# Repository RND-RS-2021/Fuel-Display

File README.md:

# Fuel-Display
Fuel Display using OLED 128x64 
# Research and Development PT. Radiator Springs Indonesia

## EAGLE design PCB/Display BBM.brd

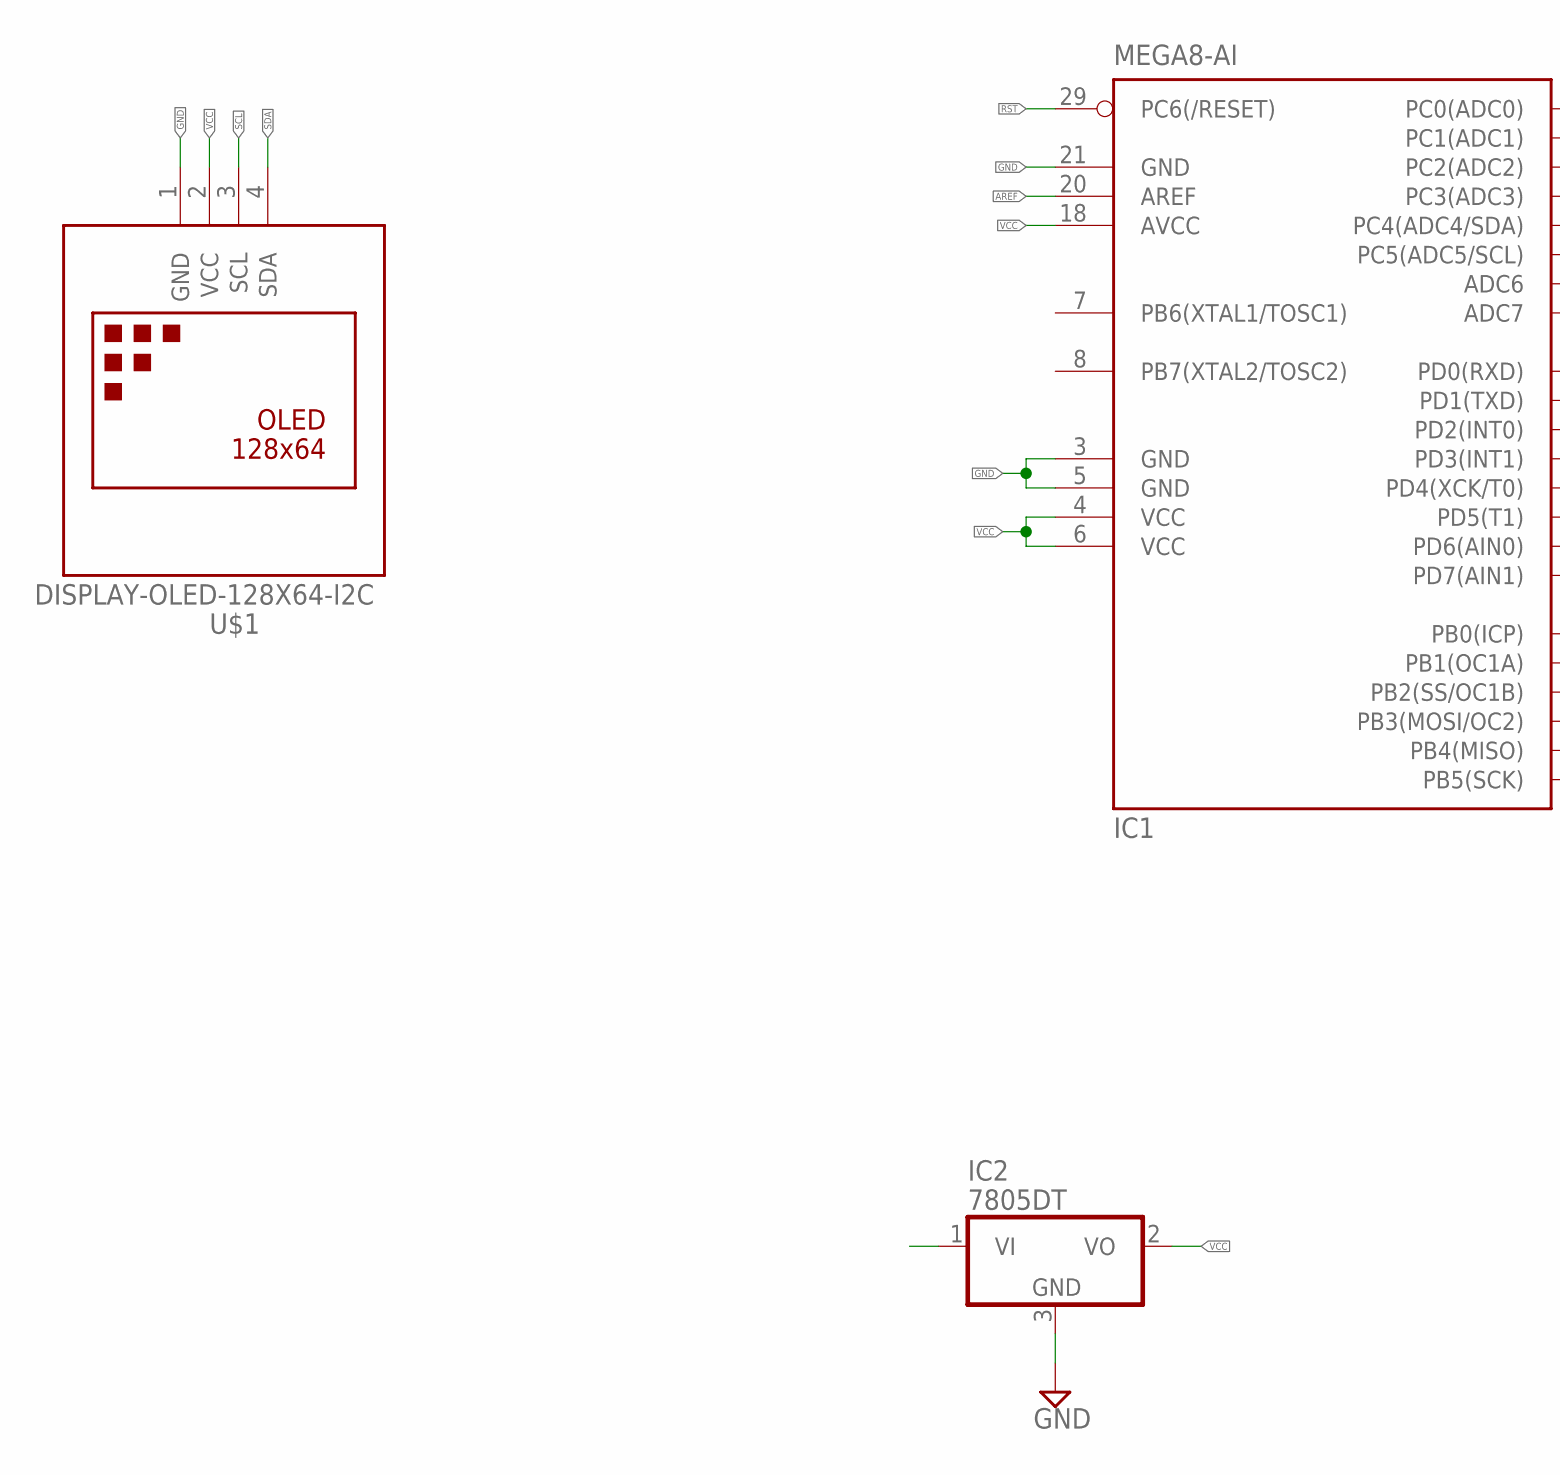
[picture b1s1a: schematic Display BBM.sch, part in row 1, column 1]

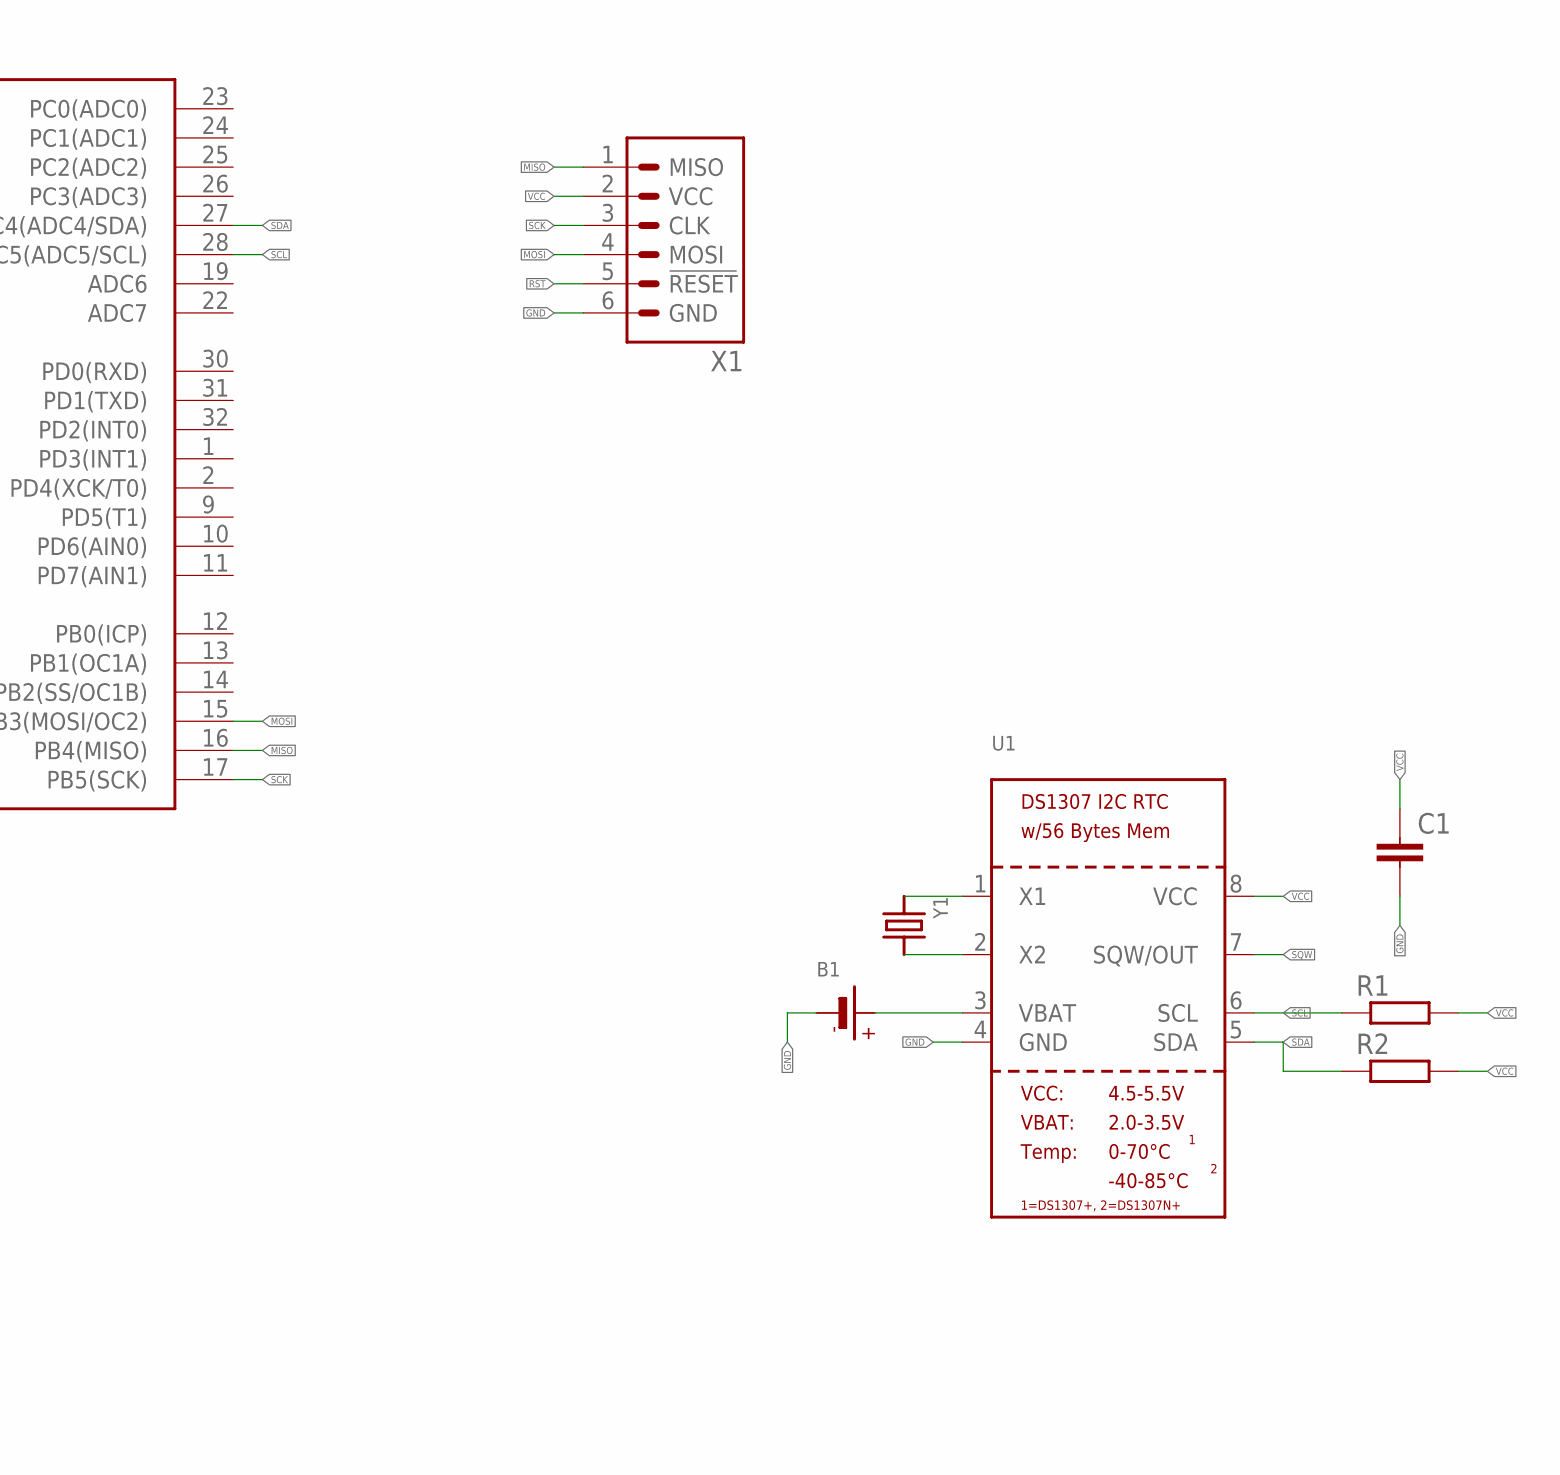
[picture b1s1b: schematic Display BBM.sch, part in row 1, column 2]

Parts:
B1: BATTERYCR1220_SMT; CR1220
C1: C-EUC0603K; C0603K
IC1: MEGA8-AI; TQFP32-08
IC2: 7805DT; TO252
R1, R2: R-EU_R0603; R0603
U1: RTC_DS1307; SOIC8_150MIL
U$1: DISPLAY-OLED-128X64-I2C
X1: MISO_MOSIIDC-06V; IDC-06V
Y1: CRYSTAL8.0X3.8; CRYSTAL_8X3.8

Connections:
AREF: IC1.20 (AREF)
GND: B1.-, C1.2, IC1.3 (GND), IC1.5 (GND), IC1.21 (GND), IC2.3 (GND), U1.4 (GND), U$1.1 (GND), X1.6 (GND)
MISO: IC1.16 (PB4(MISO)), X1.1 (MISO)
MOSI: IC1.15 (PB3(MOSI/OC2)), X1.4 (MOSI)
unnamed: U1.1 (X1), Y1.P$1 (1)
unnamed: U1.2 (X2), Y1.P$4 (2)
RST: IC1.29 (PC6(/RESET)), X1.5 (!RESET)
SCK: IC1.17 (PB5(SCK)), X1.3 (CLK)
SCL: IC1.28 (PC5(ADC5/SCL)), R1.1, U1.6 (SCL), U$1.3 (SCL)
SDA: IC1.27 (PC4(ADC4/SDA)), R2.1, U1.5 (SDA), U$1.4 (SDA)
SQW: U1.7 (SQW/OUT)
VBATT: B1.+$1 (+), U1.3 (VBAT)
VCC: C1.1, IC1.4 (VCC), IC1.6 (VCC), IC1.18 (AVCC), IC2.2 (VO), R1.2, R2.2, U1.8 (VCC), U$1.2 (VCC), X1.2 (VCC)

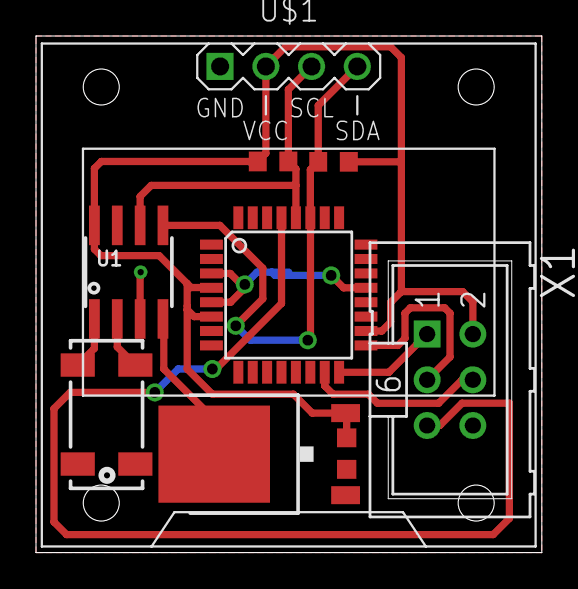
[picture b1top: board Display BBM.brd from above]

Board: 2 copper layers, 28.1 x 28.7 mm, 10 parts (1 on the bottom side), 11 nets.

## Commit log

2021-09-19 Schematic and Layout V 1.0
    Needs to tidy up the layout
2021-09-20 Add Scheme and Layout V 2.0
    Haven't place a voltage divider

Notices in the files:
parts and their libraries:
diy-modules: Released under the Creative Commons Attribution 4.0 International License: http://creativecommons.org/licenses/by/4.0
